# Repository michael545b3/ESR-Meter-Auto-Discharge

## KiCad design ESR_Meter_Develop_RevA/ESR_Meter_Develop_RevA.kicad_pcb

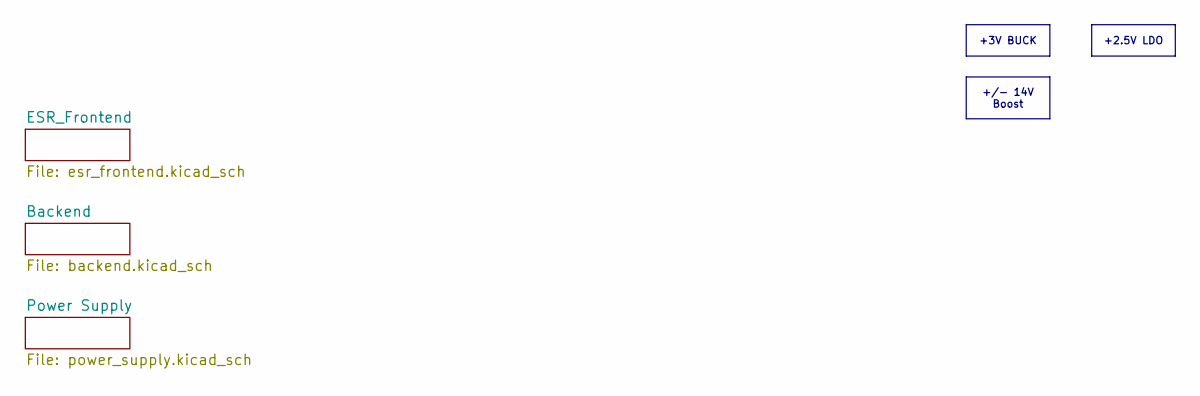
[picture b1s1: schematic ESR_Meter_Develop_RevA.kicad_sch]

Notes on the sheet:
+/- 14V Boost
+3V BUCK
+2.5V LDO

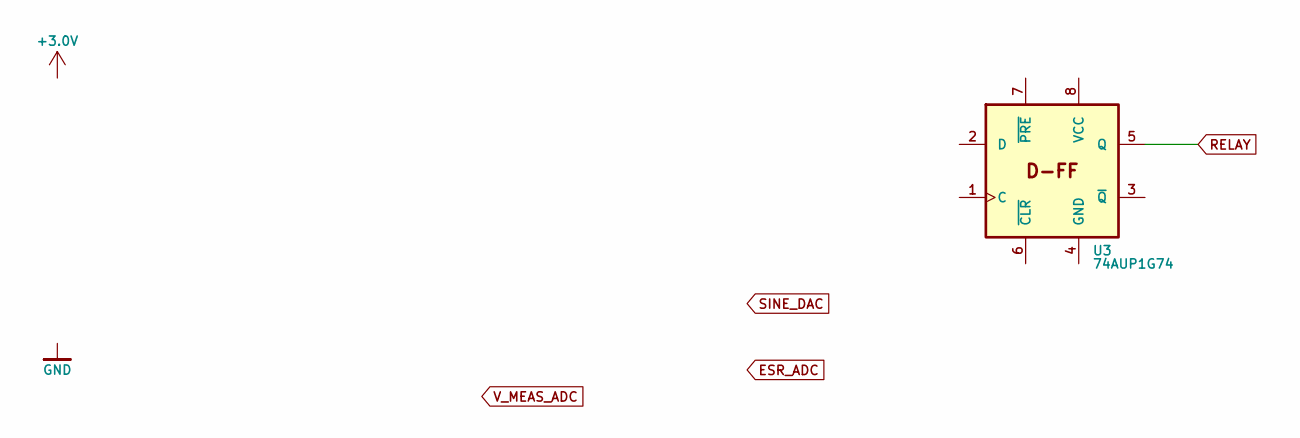
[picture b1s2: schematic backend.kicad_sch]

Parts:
U3: 74AUP1G74; VSSOP-8_2.3x2mm_P0.5mm; MPN 74AUP1G74DC,125

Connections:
RELAY: U3.5 (Q); also elsewhere on the board

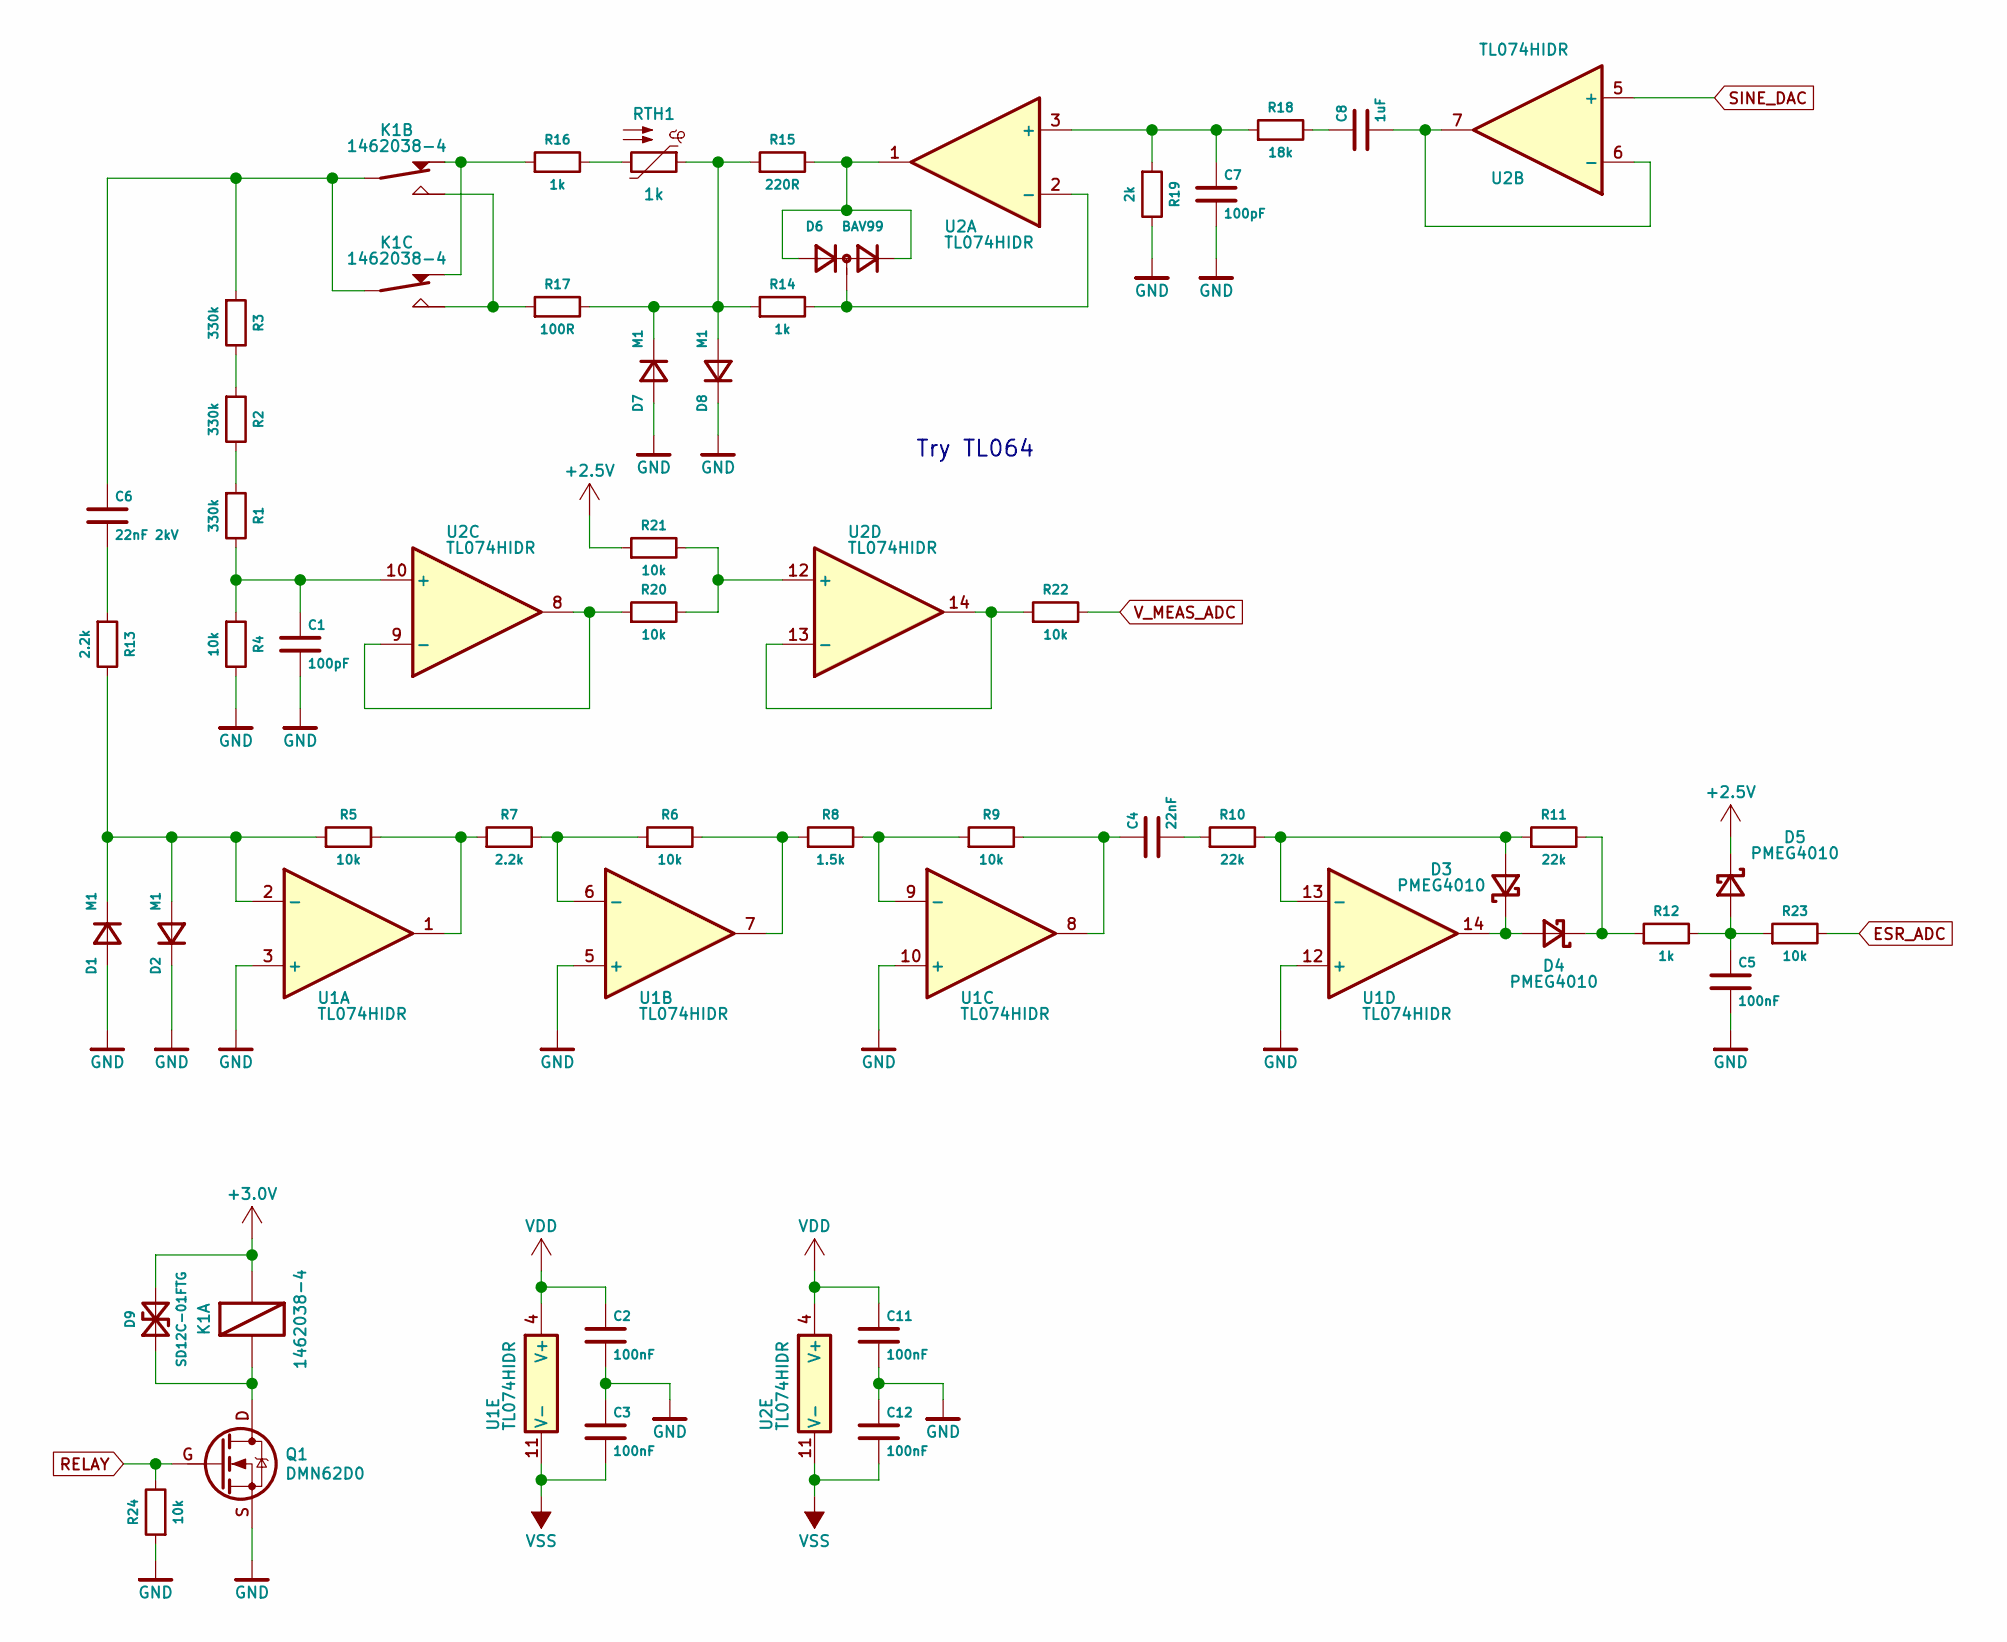
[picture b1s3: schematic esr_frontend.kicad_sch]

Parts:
C1, C7: 100pF; C_0603
C2, C3, C5, C11, C12: 100nF; C_0603; MPN C0603C104K5RACAUTO
C4: 22nF; C_0603
C6: 22nF 2kV; C_1812; MPN CHV1812N2K0223KXT
C8: 1uF; C_0603; MPN UMK107AB7105KA-T
D1, D2, D7, D8: M1; D_SMA; MPN M1
D3, D4, D5: PMEG4010; D_SOD-123; MPN PMEG4010ETR,115
D6: BAV99; SOT-23_ACAC; MPN BAV99
D9: SD12C-01FTG; D_SOD-323_Bipolar; MPN SD12C-01FTG
K1: 1462038-4; AXICOM_Relay_IM; MPN 1462038-4
Q1: DMN62D0; SOT-23_GSD; MPN DMN62D0U-7
R1, R2, R3: 330k; R_1206
R4, R5, R6, R9, R20, R21, R22, R23, R24: 10k; R_0603; MPN RMCF0603FT10K0
R7: 2.2k; R_0603
R8: 1.5k; R_0603
R10, R11: 22k; R_0603
R12, R14: 1k; R_0603; MPN RMCF0603FT1K00
R13: 2.2k; R_1210
R15: 220R; R_0603; MPN RC0603FR-07220RL
R16: 1k; R_Axial__L17.0mm_D6.0mm_P25.40mm_H
R17: 100R; R_1210
R18: 18k; R_0603
R19: 2k; R_0603
RTH1: 1k; PTCEL13; MPN PTCEL13R102STE
U1, U2: TL074HIDR; SOIC-14; MPN TL074HIDR

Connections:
+2.5V: D5.C, R21.1
+3.0V: D9.A2, K1.1 (+)
ESR_ADC: R23.2
GND: C1.2, C2.2, C3.1, C5.2, C7.2, C11.2, C12.1, D1.A, D2.C, D7.A, D8.C, Q1.S, R4.2, R19.2, R24.1, U1.3 (+), U1.5 (+), U1.10 (+), U1.12 (+)
unnamed: C4.1, R9.2, U1.8
unnamed: C4.2, R10.1
unnamed: C5.1, D5.A, R12.2, R23.1
unnamed: C6.1, K1.3, K1.6, R3.1
unnamed: C6.2, R13.1
unnamed: C8.1, R18.2
unnamed: D3.C, D4.A, U1.14
unnamed: D4.C, R11.2, R12.1
unnamed: D6.A, D6.C, R15.2, U2.1
unnamed: D7.C, D8.A, R14.1, R15.1, R17.2, RTH1.1
unnamed: D9.A1, K1.8, Q1.D
unnamed: K1.2, K1.7, R16.1
unnamed: K1.4, K1.5, R17.1
unnamed: R1.1, R2.2
unnamed: R2.1, R3.2
unnamed: R5.2, R7.1, U1.1
unnamed: R6.2, R8.1, U1.7
unnamed: R16.2, RTH1.2
unnamed: D1.C, D2.A, R5.1, R13.2, U1.2 (-)
unnamed: R6.1, R7.2, U1.6 (-)
unnamed: R8.2, R9.1, U1.9 (-)
unnamed: D3.A, R10.2, R11.1, U1.13 (-)
unnamed: C7.1, R18.1, R19.1, U2.3 (+)
unnamed: D6.AC, R14.2, U2.2 (-)
unnamed: C8.2, U2.6 (-), U2.7
unnamed: C1.1, R1.2, R4.1, U2.10 (+)
unnamed: R20.1, U2.8, U2.9 (-)
unnamed: R20.2, R21.2, U2.12 (+)
unnamed: R22.1, U2.13 (-), U2.14
RELAY: Q1.G, R24.2; also elsewhere on the board
SINE_DAC: U2.5 (+)
VDD: C2.1, C11.1, U1.4 (V+), U2.4 (V+)
VSS: C3.2, C12.2, U1.11 (V-), U2.11 (V-)
V_MEAS_ADC: R22.2

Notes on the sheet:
Try TL064

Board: 2 copper layers, 49 parts (0 on the bottom side), 35 nets, no tracks yet.

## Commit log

2026-03-23 init comit
2026-03-23 working on frontend
2026-03-27 bckp
2026-04-07 backup WIP
